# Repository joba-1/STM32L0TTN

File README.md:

# STM32L0TTN

Send BME280 data and voltage to TTN with STM32L0

## Build

* Download and install STM32CubeIDE (as of now version 1.4.2)
* Import this repo
* Open .ioc file and select "Project/Generate Code" (should download needed "firmware" files for the chip from ST)
* Build Release or Debug (currently RAM 95%, FLASH 88% used)

## Wiring

connect Gnd of all components

### STM32L011

Not checked without, but generally recommended to use a small ceramic (~10nF) and big electrolyt condensator (~10µF) between + and - near STM pins

* Look at the ioc file with CubeMX pinout view.
* Vdd _and_ Vdda to 1.8-3.3V
* Vss to Gnd
* PB9-Boot0 pulled to Gnd (~10k) to safely boot from flash
* STLink for flashing and debug: SWD, SWC, Gnd, NRst (and could provide Vdd via JP1)

### BME280

* SDA=MOSI, SDC=MISO, others should be obvious

### RFM95W

* Ant=~8cm wire (vary length and position to get best average RSSI as reported by TTN)
* NSS=CS, others should be obvious (DIO0, DIO5, MOSI, MISO, SCK and RESET)

RFM95W pin labels for reuse of ESP32 adapter breadboard (print with 600dpi)

### Serial

Rx of a usb to serial converter sends at 115200. I use this command (serial port name ttyUSB_ser_red is defined in my /etc/udev/rules.d)
    pio device monitor -p /dev/ttyUSB_ser_red -b 115200

### LED

can be used without resistor. I use 1kOhm to save battery

## References

Good resource for STM32 is [Stefan Frings](http://stefanfrings.de/stm32/stm32l0.html)
He has links to reference, datasheet, errata and more. E.g.:

* [STM32L011 Datasheet](https://www.st.com/resource/en/datasheet/stm32l011d3.pdf)
* [STM32L011 Reference](https://www.st.com/resource/en/reference_manual/dm00108282-ultra-low-power-stm32l0x1-advanced-arm-based-32-bit-mcus-stmicroelectronics.pdf)
* [STM32L011 Errata](https://www.st.com/resource/en/errata_sheet/dm00237371-stm32l011x3-4-device-limitations-stmicroelectronics.pdf)
* [Power consumption](http://www.st.com/content/ccc/resource/technical/document/application_note/27/58/8e/81/79/fb/4f/ac/DM00108286.pdf/files/DM00108286.pdf/jcr:content/translations/en.DM00108286.pdf)

## Power Info Bits

* Examples for LL are here: STM32Cube/Repository/STM32Cube_FW_L0_V1.11.2/Projects/NUCLEO-L073RZ/Examples_LL/RTC/RTC_ExitStandbyWithWakeUpTimer
* Periodic wakeup timer is in Reference 22.4.6 (Periodic auto-wakeup)
* 1s to 18h periodic wakeup with ck_spre = 1s (see 22.4.3) and WUCKSEL [2:1] = 10
* Enable by WUTE bit in RTC_CR register
* Once setup it runs in normal and low power. 
* Sets WUTF flag in RTC_ISR if elapsed and reloads RTC_WUTR (timer counter). User resets WUTF
* Set WUTIE bit in RTC_CR to generate interrupt to wake up from low power modes
* System reset and Sleep, Stop, Standby have no influence on the WUT (wakeup timer)
* Save Lora frame counter in backup register: Reference 22.7.20 RTC backup registers (RTC_BKPxR)
* I couldnt make it work with LL lib, had to use big fat HAL for RCC and RTC. What is missing?

        LL_RTC_DisableWriteProtection(RTC);
        LL_RTC_WAKEUP_Disable(RTC);
        while( !LL_RTC_IsActiveFlag_WUTW(RTC) );
        LL_RTC_WAKEUP_SetClock(RTC, LL_RTC_WAKEUPCLOCK_CKSPRE);
        LL_RTC_WAKEUP_SetAutoReload(RTC, 3); // wake up every 3+1 s
        LL_RTC_EnableIT_WUT(RTC);
        LL_RTC_WAKEUP_Enable(RTC);
        LL_RTC_EnableWriteProtection(RTC);
        while( LL_RTC_IsActiveFlag_WUTW(RTC) );
        LL_RTC_ClearFlag_WUT(RTC);
        NVIC_ClearPendingIRQ(RTC_IRQn);

## Status

Works fine.
Power consumption much lower than with my similar ATTiny84 board

TTN migrated from V2 to V3. After they reactivated the device id ranges of the old network I could register the devices with the same devId, AppsKey and NwsKey.
After ~2 weeks the devices started showing up in the console -> code works unchanged with V3! Config example in this post: https://www.thethingsnetwork.org/forum/t/migrate-old-abp-device-to-v3

## Done
Not needed. by far the most power is consumed by sending. These tasks are not relevant
* Sleep while waiting for sensor or transmitter (90% of the ~100ms active cycle is waiting)
* Cut power of sensor and transmitter between measurements? Standby consumption is already quite low.
Works fine for a long time now. No problems so far
* Check recommended hookup of STM32L011K4 (capacitors, boot mode lines, reset, ...?). Since it works, it is probably ok as described above :)

## Todo
* PCBs for coin cell or 2xAAA: coin cell not at all good at low temp -> abandoned for BMP280 (outdoor) variants
* 3D-printed housings

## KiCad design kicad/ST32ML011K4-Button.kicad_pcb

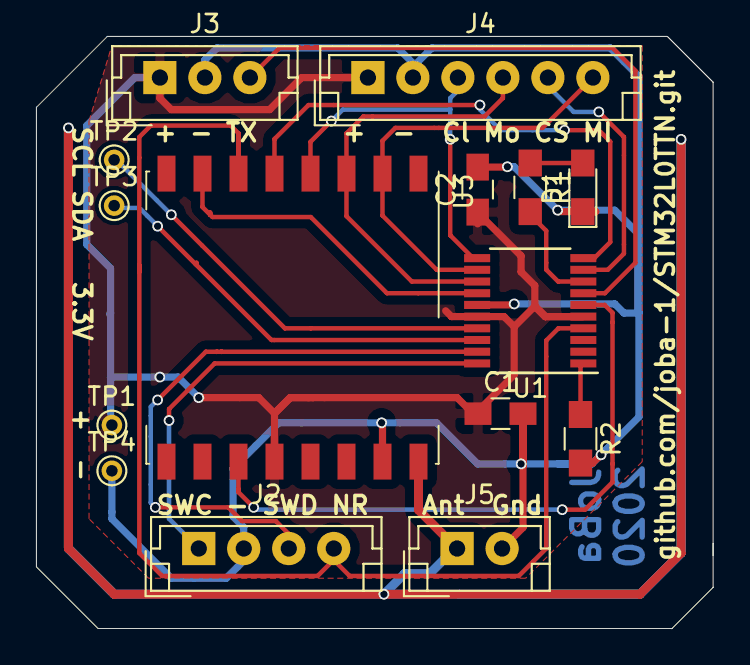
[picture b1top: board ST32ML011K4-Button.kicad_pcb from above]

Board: 2 copper layers, 37.6 x 32.9 mm, 16 parts (1 on the bottom side), 19 nets.

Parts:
C1, C2: 100nF; C_0805_HandSoldering
D1: LED; LED_0805_HandSoldering
J1: Conn_01x02_Male; Keystone_1058_1x2032-CoinCell
J2: Conn_01x04_Male; JST_EH_B04B-EH-A_04x2.50mm_Straight
J3: Conn_01x03_Male; JST_EH_B03B-EH-A_03x2.50mm_Straight
J4: Conn_01x06_Male; JST_EH_B06B-EH-A_06x2.50mm_Straight
J5: Conn_01x02_Male; JST_EH_B02B-EH-A_02x2.50mm_Straight
R1: 470; R_0805_HandSoldering
R2: 10k; R_0805_HandSoldering
TP1, TP2, TP3, TP4: TEST; PINTST
U1: STM32L031F4Px; TSSOP-20_4.4x6.5mm_Pitch0.65mm
U3: RFM9X; Hopref_RFM9XW_SMD

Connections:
+3V3: C1.1, C2.1, J1.1, J3.1, J4.1, TP1.1, U1.5, U1.16, U3.12
BME_CS: J4.5, U1.9
Earth: C1.2, C2.2, D1.1, J1.2, J2.2, J3.2, J4.2, J5.2, R2.2, TP4.1, U1.15, U3.15
MISO: J4.6, U1.12, U3.2
MOSI: J4.4, U1.13, U3.3
NRESET: J2.4, U1.4, U3.6
unnamed: D1.2, R1.1
unnamed: J5.1, U3.16
unnamed: R1.2, U1.8
unnamed: R2.1, U1.1
RFM_CS: U1.10, U3.5
RX_READY: U1.14, U3.7
SCK: J4.3, U1.11, U3.4
SCL: TP2.1, U1.17
SDA: TP3.1, U1.18
SWCLK: J2.1, U1.20
SWDIO: J2.3, U1.19
TX: J3.3, U1.7
TX_READY: U1.6, U3.11

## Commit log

2020-09-10 working RTC/Standby example
2020-09-10 IOC file ready (using HAL)
2020-09-10 switch gpio, lpuart, adc and spi to LL, add bme280
2020-09-10 check bme280 for sane values
2020-09-10 add rfm95 and lorawan (not sending again...)
2020-09-10 set all CS high before using SPI
2020-09-11 quiet after 10th frame, 2 -> 1 MHz clock
2020-09-11 add readme and use repo name as project name
2020-09-11 readme about failed standby using LL
2020-09-11 Add current ram and flash size
2020-09-11 settle adc: use after bme, print standby time and version
2020-09-11 condensator capacity can be smaller
2020-09-14 mention dl of fw
2020-09-14 ignore .mxproject and .settings/language.settings.xml
2020-09-15 PCB for 2xAAA and 2032 button cell
2020-09-16 gerber files V1 as sent to pcbway
2020-09-16 undo autosave edits for 4x...
2020-09-16 add 3d view of pcb
2020-10-14 add delay before first send
2020-10-14 now that prototype works: obsolete pcb files - need rework
2021-08-26 Add STM32 TSSOP20 pinout to readme
2021-08-26 Add RFM95W pin labels to readme
2022-01-18 add note for TTN V2 -> V3 migration
